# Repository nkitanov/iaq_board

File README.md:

# IAQ (Indoor Air Quality) Board 
IAQ Board is a DIY (Do-It-Yourself) device for measuring internal air quality. I needed a device for measuring some air quality parameters which is **compact, cheap, simple and capable**. After I prototyped it, decided instead of mounting into some odd box with cables hanging inside between the sensors, why not just solder everything on a printed circuit board. I had some experience with this from the time when I was a student years ago and luckily now it's much easier to crate PCB and very cheap to get it printed. 

**And here is my device. I am publishing all the details and documentation under '[open source hardware](https://en.wikipedia.org/wiki/Open-source_hardware)' CC-BY-CA license, so everyone can build, adapt and sell it, as long as share under the same license**
s
**Table of Contents**
   * [IAQ (Indoor Air Quality) Board](#iaq-indoor-air-quality-board)
      * [What exactly is this thing?](#what-exactly-is-this-thing)
      * [Who can build it?](#who-can-build-it)
      * [What about ordering a device?](#what-about-ordering-a-device)
   * [Components Details](#components-details)
      * [1. PCB](#1-pcb)
      * [2. Holder case](#2-holder-case)
      * [3. Microcontroller Board](#3-microcontroller-board)
      * [4. Dust Sensor](#4-dust-sensor)
      * [5. CO2 sensor](#5-co2-sensor)
      * [6. Temperature/Humidity/Pressure sensor](#6-temperaturehumiditypressure-sensor)
      * [7. Ambient Light Sensor](#7-ambient-light-sensor)
      * [8. LEDs](#8-leds)
      * [9. Displays](#9-displays)
      * [10. Volatile Organic Compound sensor](#10-volatile-organic-compound-sensor)
      * [11. Other electrical components](#11-other-electrical-components)
      * [Can you skip components?](#can-you-skip-components)
   * [Bill of Materials (BOM)](#bill-of-materials-bom)
   * [Firmware](#firmware)
   * [Schematic](#schematic)
   * [Soldering tips](#soldering-tips)
   * [User manual](#user-manual)
         * [Multi function button](#multi-function-button)
         * [LED Brightness control and correction](#led-brightness-control-and-correction)
   * [FAQ](#faq)
            * [<em>Can I power it from a battery?</em>](#can-i-power-it-from-a-battery)
            * [<em>Can it be installed outdoors?</em>](#can-it-be-installed-outdoors)
            * [<em>How to calibrate MH-Z19B CO2 sensor?</em>](#how-to-calibrate-mh-z19b-co2-sensor)
            * [<em>How to calibrate SGP30 VOC sensor?</em>](#how-to-calibrate-sgp30-voc-sensor)
            * [<em>How to connect to WiFi?</em>](#how-to-connect-to-wifi)
            * [<em>How to add it in Home Assistant?</em>](#how-to-add-it-in-home-assistant)
            * [<em>What if some of the sensors/displays is disconnected while the device works?</em>](#what-if-some-of-the-sensorsdisplays-is-disconnected-while-the-device-works)
         * [<em>What about short circuits of the exposed electronics?</em>](#what-about-short-circuits-of-the-exposed-electronics)
   * [More Tech Details](#more-tech-details)
   * [Known issues](#known-issues)
   * [License](#license)

## What exactly is this thing?
The device is based on widely available and cheap essential components ([MCU](https://en.wikipedia.org/wiki/Microcontroller) and sensors). The core component is a simple [PCB](https://en.wikipedia.org/wiki/Printed_circuit_board) (printed circuit board) that's why I called it **IAQ Board**. The board integrates all the components in a very small footprint (size of a cigarette box). All parts are soldered on it and everyone can assemble it with basic soldering skills. The total price if you build it yourself is about 50-60 EUR. I also made simplistic holder for 3D print (6-7 EUR is you don't have a 3D printer). For these amount of money you get the following air parameters measured adequately (you might not install all sensors if you want to save money): 
- [X] ***Temperature / Humidity / Pressure***
- [X] [***Air particles PM1, PM2.5, PM10***](https://en.wikipedia.org/wiki/Particulates)
- [X] [***Carbon Dioxide with NDIR sensor***](https://en.wikipedia.org/wiki/Indoor_air_quality#Carbon_dioxide)
- [X] [***Air Quality Index by EPA, based on 24h average PM2.5 particles***](https://airindex.eea.europa.eu/Map/AQI/Viewer/)
- [X] [***Ambient light***](https://en.wikipedia.org/wiki/Illuminance)
- [X] [***Total VOC (volatile organic compound)***](https://en.wikipedia.org/wiki/Volatile_organic_compound)
- [X] ***equivalent CO2 (not very correct compared with the NDIR sensor, but it's provided by the VOC sensor)***

**On top of that:**
- [X] ***At least one OLED display to show the data (can have one more on the top of the MCU board)***
- [X] ***three RGB wide angle LEDs with auto brightness. LED1 indicates PM2.5, LED2 - Air quality index, LED3 - CO2.*** 
- [X] ***auto night dimming of the displays and LEDs (can be disabled)***
- [X] ***MIN/MAX values of Temperature, PM2.5 and CO2, and 24h average PM2.5 value.***
- [X] ***multi function button for selection of the data to show on the display***
- [X] ***[firmware](https://en.wikipedia.org/wiki/Firmware) based on [ESPhome](https://esphome.io/), the device can be [directly added](https://esphome.io/components/api.html) in [Home Assistant](https://www.home-assistant.io/)***
- [X] ***WiFi access to the device with http server and [REST API](https://esphome.io/web-api/index.html) and [esphome native API](https://esphome.io/components/api.html)  to read the sensor data***

Here is a video with all you need to know:

## Who can build it?
The device is just a simple PCB board and almost everyone with some soldering skills can assemble it in a few steps:
1. [Download the PCB files](kicad/) and print the PCB somewhere like https://jlcpcb.com/
2. Buy some components (listed in the bill of materials section) from Aliexpress or any other source.
3. Solder everything on the board. With the exception of the ambient light sensor, all the rest is pretty easy with general soldering skills. Soldering light sensor can be done with regular soldering iron, but because of the small size of the IC, it's easier if you have heat gun or SMD reflow oven/plate. [Here is video how to complete device from assembled PCB.](https://www.youtube.com/watch?v=b2oDBgN3h1w)
4. Flash the microcontroller with the esphome firmware [following the manual](firmware/). You can write your own firmware if you have the skills. :smile: 
5. Print the holder case on 3D printer if you wish. I have some sensors without it and they are perfectly fine, so it's up to you.

If you have experience with electronics and microcontrollers just check the [schematics](kicad/) and make whatever you wish - build your own firmware, do another PCB, connect external sensors, don't use it at all because you can make it better :smile:. The device is quite simple for embedded electronics enthusiasts anyway...

## What about ordering a device?
I made this device for me and then decided to share it. I think a lot of people might be interested to have such air quality sensor. I did not have intension to make money from it, that's why it's "open hardware" and I publish all of the information, so everyone can build it. 

However I know that someone might be interested in the device, but lack the skills to build it. [Please follow this link for more details.](ordering.md)

# Components Details
The device with AAA battery size comparison:

## 1. PCB

The PCB (printed circuit board) is very simple and compact. It's 70x43mm (photos above are showing it larger than the actual size). It just connects a few sensors, microcontroller and displays. I wanted to integrate it in as much smaller footprint as possible, so the whole device is like a cigarette box. Most of the parts are surface mounted which makes the soldering just a bit more complicated, but still not a big deal. And of course it could be integrated even more by soldering all individual components on the PCB but then it's not really a hobby project anymore and much more difficult to build it.
It's designed on [KiCad](https://kicad.org/) and in the [kicad folder](kicad/) you can find full KiCad project, PCB gerber files, etc.
## 2. Holder case

For any device the box is important. However my idea was to expose the PCB and electronics as much as possible in order to simplify it. I like the "raw" view of electronics and in this form I find it beautiful. 

Taking into account this, I designed a simple holder case for "sliding" the PCB in it and holding the particle sensor. The case can stay at about 45 degrees angle. It is designed on Fusion 360 and the [details are here](case_model). The holder case is not perfect, I was thinking to redesign it but no time for this. I am sure someone can do it better. :smile: Or design a complete box to cover the electronics fully, for me it is better in this minimalistic style. 
## 3. Microcontroller Board

Initially I developed the board with using the most popular WiFi enabled MCU [ESP8266](https://en.wikipedia.org/wiki/ESP8266) mounted on the cheap and small [Wemos D1 Mini board](https://docs.wemos.cc/en/latest/d1/d1_mini.html). However this MCU have some limitations described in the [tech details](#more-tech-details), so I changed it with the same size board compatible with Wemos D1 Mini, but running the newer much more powerful MCU of the same company - [ESP32](https://en.wikipedia.org/wiki/ESP32). In that way the device is quite stable, can run web server and since the board is having the same layout, on top of the D1 Mini ESP32 board you can connect extra display designed for d1 mini very easy. PCB is compatible with both D1 Mini ESP8266 or ESP32, even the labels are the same like on the older D1 board. However **I do not recommend to use D1 mini with ESP8266!** Also if I have to build next version of the PCB (I still have some 25 pcs), I will change the pins of one of the dust sensors.

These small size MCU board are pretty nice, they are tiny, have USB connector, onboard power supply and USB converter for programming or serial output. And you are powering the whole device just with a mini USB cable.
## 4. Dust Sensor

Dust sensor is the Chinese [Plantower PMS7003]([http://www.plantower.com/en/content/?110.html](https://www.plantower.com/en/products_33/76.html)) - 1, 2.5 and 10 micron particle laser sensor. It's very small and is perfect for indoor environment. 
## 5. CO2 sensor

Carbon dioxide sensor is the Chinese [Winsen MH-Z19B](https://www.winsen-sensor.com/sensors/co2-sensor/mh-z19b.html) - the most expensive part of the device. It's quite popular for hobby air quality meters and can [adequatly measure](https://www.circuits.dk/testing-mh-z19-ndir-co2-sensor-module/) up to 5000 ppm CO2 concentration.

**Keep in mind that there are some fake MH-Z19B sensors, [explained here](https://revspace.nl/MH-Z19B#Fake_MH-Z19B_.28black_PCB.29).**
## 6. Temperature/Humidity/Pressure sensor

This sensor is the popular [Bosch BME280](https://www.bosch-sensortec.com/products/environmental-sensors/humidity-sensors-bme280/), mounted on 3.3V only breakout board from China. There are also smaller [breakout boards](http://www.cncroutersource.com/breakout-boards.html) from China working both on 5V and 3.3V, but these have voltage regulator which can theoretically warm the board and change the temperature reading. That's why I use the boards with 3.3V only.

**Please note that due to semiconductor shortage these are difficult to find now (June 2021). I am currently using my own breakout where I solder the BME directly. BME280 as IC can be found occasionally in stock from DigiKey**
## 7. Ambient Light Sensor

The light sensor is [TSL 2561](https://ams.com/tsl2561) and it's the only sensor you need to solder directly on the board without a breakout board. I added this sensor not because I need to measure the ambient light but because I am a brightness freak, and I need the LEDs brightness to depend on the ambient light. Also wanted during the night when the lights are off the device to turn off the LEDs and displays automatically. You can also change the behavior of this brightness control and I spend some extra time developing the config only for the brightness features. :smile:
## 8. LEDs

The device have three [Neopixel 5050](https://www.digikey.com/catalog/en/partgroup/neopixel-rgb-5050-led-with-integrated-driver-chip-100-pack/70939) RGB multicolor LEDs. These LEDs are mostly found in the colorful LED strips and are controlled over a single wire. In my esphome based firmware left LED color is indicating the level of PM2.5 and change the colors depending on the value. Middle (LED2) indicates Air Quality Index based on PM2.5 only and the right one (LED3) indicates CO2 value. Keep in mind PM2.5 values are close to [EEA](https://www.eea.europa.eu/) levels (especially AQI). Some other devices like Xiaomi Air Purifiers have some very high levels on their displays and logic - it's green up to 70 microns which is already considered unhealthy both by EEA and EPA. In China "healthy" is considered bellow 50 microns. That's why AUTO mode of these Chinese devices [works so bad](https://smartairfilters.com/en/blog/xiaomi-auto-mode-leaves-air-unsafe-86-hours/). I try to keep indoor PM2.5 around 5-10 microns. I normally control my purifiers by Home Assistant and do not rely on their auto logic. If you have Xiaomi Purifier it can still show green, and the iaq device shows stable red, but it is correct according to the EU regulations.

**Colors of the LEDs depends on this table:**
PM2.5 value (um/m3)<br>LED 1 | [AQI by EEA (Air Quality Index for PM2.5 24h average)](https://airindex.eea.europa.eu/Map/AQI/Viewer/)<br>LED 2 | CO2 value (ppm)<br>LED 3 | Color |  R  |  G  |  B
:-----------------: | :-------------: | :-------------: | :---: | :-: | :-: | :-: 
< 10 | < 10 (Good) | < 700 |  | off | on | off 
11 - 20 | 10 - 20 (Fair) | 700 - 1000 |  | off | on | on 
20 - 30 | 20 - 25 (Moderate) | 1000 - 1500 |  | on | on | off 
30 - 40 | 25 - 50 (Poor) | 1500 - 2100 |  | on | off | on 
\> 50 | > 50 (Very Poor) | > 2100 |  | on | off | off 

## 9. Displays
The main display is the popular SSD1306 128x64 OLED display. On the top of the MCU board you can install extra [OLED 63x48](https://docs.wemos.cc/en/latest/d1_mini_shiled/oled_0_66.html) shield from Lolin which shows temperature, humidity and air pressure only.
## 10. Volatile Organic Compound sensor

This is the [Sensirion SGP30](https://www.sensirion.com/en/environmental-sensors/gas-sensors/sgp30/) senor mounted on a breakout board from China. I do not use it on all my devices, but I added it because I can. :smile: Also with it the device measures almost completely the internal air quality. SGP30 is also showing equivalent CO2 based on VOC but it's not precise compared with MH-Z19B NDIR sensor. Also it needs periodic calibration hardcoded in the firmware which makes it more tricky to use.

Please [check here](https://github.com/nkitanov/iaq_board/issues/10#issuecomment-798994427) for the known issues with these boards.
## 11. Other electrical components

The device have 2 buttons - one for selection screens and settings, and another micro button for calibration of the CO2 sensor to 400ppm if you keep it pressed for more than 7 sec. 

There are also four [surface mounted](https://en.wikipedia.org/wiki/Surface-mount_technology) [bypass capacitors](https://en.wikipedia.org/wiki/Decoupling_capacitor) for the ambient light sensor and the LEDs.

## Can you skip components?
Yes. The minimum you need is the [microcontroller board](#3.-microcontroller-board). However since you don't have any sensors, you won't get any data. :smile: You can add only the sensors needed. Also if you skip ambient light sensor there will be no auto brightness control and the LEDs will operate always at 25% intensity. Installing only the ambient light sensor without any of the displays or any of the other [I2C](https://en.wikipedia.org/wiki/I%C2%B2C) sensors (BME280, SGP30) will not work as there are no [pullup resistors](https://en.wikipedia.org/wiki/Pull-up_resistor) on the PCB for the I2C bus since it uses the resistors of the external breakout boards.

# Bill of Materials (BOM)
Bellow is the list of all parts needed to assemble the device with links to sources where you can get them. Of course other sources can be used, just pay attention that the items are identical with the listed bellow. For example the SSD1306 display can be found with similar physical look and dimensions, but pins are not the same.

Schematic Ref | ITEM | pcs | Comment
--------------| ---- | :-: | -------
| | PCB Board | 1 | in [kicad folder](kicad) you can find all the data and GERBER PCB design files
U1 | [WeMos_D1_mini_ESP32](https://www.aliexpress.com/item/4000880936043.html?spm=a2g0o.productlist.0.0.f387754egZVnTc&algo_pvid=b105e43b-6669-40bc-99c4-cf22d026995d&algo_expid=b105e43b-6669-40bc-99c4-cf22d026995d-6&btsid=0bb0623616009843570355505e4ca0&ws_ab_test=searchweb0_0,searchweb201602_,searchweb201603_) | 1 | [ESP8266 version](https://www.wemos.cc/en/latest/d1/d1_mini.html) also can work but not recommended 
U2 | [PMS7003 Sensor](https://www.aliexpress.com/item/32832444694.html?spm=a2g0s.9042311.0.0.27424c4dKxsO6Z) | 1 | don't use the 2x5pin 1.27mm receptacle which comes normally wit these sensors, explanation is bellow
U3 | [SSD1306 Display](https://www.aliexpress.com/item/32956051129.html?spm=a2g0o.productlist.0.0.523365fcQkP3XC&algo_pvid=b62bd3ab-fe19-479e-bc50-b2c68dd35525&algo_expid=b62bd3ab-fe19-479e-bc50-b2c68dd35525-25&btsid=67d67e08-4ad1-4c08-8cec-e378bae47fc6&ws_ab_test=searchweb0_0,searchweb201602_9,searchweb201603_55) | 1 | pay attention to correct pin order if you are buying from another source, as there are similar 4pin boards with different pinout
U4 | [BME280 breakout board](https://www.aliexpress.com/item/4000166540445.html?spm=a2g0o.productlist.0.0.363a562ely2LZq&algo_pvid=b0bd6068-edbb-4f9c-aa24-92324f726eda&algo_expid=b0bd6068-edbb-4f9c-aa24-92324f726eda-8&btsid=3927b67d-2f89-4594-9f47-b017e00ef8a0&ws_ab_test=searchweb0_0,searchweb201602_9,searchweb201603_55) | 1 | only 3.3V version with 6 pins which have both I2C and SPI. **Please note that due to semiconductor shortage these are difficult to find now (June 2021). I am currently using my own breakout where I solder the BME directly. BME280 as IC can be found occasionally in stock from DigiKey**
U5 | [MH-Z19B Sensor](https://www.aliexpress.com/item/1005001865093513.html?spm=2114.12010610.8148356.5.5b7387a5ZmuUlX) | 1 | **Beware for fake sensors, as [explained here](https://revspace.nl/MH-Z19B#Fake_MH-Z19B_.28black_PCB.29). Buy from Winsen official store in Aliexpress.**  
U6 | [SGP30 breakout board](https://www.aliexpress.com/item/4000004614708.html?spm=a2g0o.productlist.0.0.688164abtt6ZRA&algo_pvid=7f813f70-3c1d-42ee-b6cf-9bf501c47314&algo_expid=7f813f70-3c1d-42ee-b6cf-9bf501c47314-1&btsid=3f683b7d-631a-4373-b0a1-f574cd317549&ws_ab_test=searchweb0_0,searchweb201602_9,searchweb201603_55) | 1
U7 | [TLS2561 light sensor](https://www.aliexpress.com/item/33056165996.html?spm=a2g0s.9042311.0.0.15314c4draqb6x) | 1
C1-C4 | [0.1 uF SMD Capacitor](https://bg.farnell.com/wurth-elektronik/885012207016/cap-0-1-f-10v-10-x7r-0805/dp/2534051?st=smd%20capacitors) | 4
D1-D3 | [Neopixel 5050 LED](https://www.aliexpress.com/item/4000750610574.html?spm=a2g0o.productlist.0.0.55a96722mpqDCp&algo_pvid=4be2d94a-875a-4e56-af12-1f6a3dcdf49f&algo_expid=4be2d94a-875a-4e56-af12-1f6a3dcdf49f-5&btsid=0bb0623416009856118282154ebe61&ws_ab_test=searchweb0_0,searchweb201602_,searchweb201603_) | 3
| SW1 | [Tactile Switch B3S-1000](https://uk.farnell.com/omron/b3s-1000/switch-spno-0-05a-24v-smd/dp/177807) | 1 |
| SW2 | [Tactile Switch B3U-1000P](https://bg.farnell.com/omron/b3u-1000p/switch-spst-no-0-05a-12v-smd/dp/1333652?st=B3U-1000P) | 1
| | [PCB Receptacle, 1.27 mm, 10 Contacts](https://bg.farnell.com/amphenol-icc-fci/20021311-00010t4lf/receptacle-vert-1-27mm-tht-10way/dp/1865313) | 1 | This PCB Receptacle is for connecting PMS7003 dust sensor. Keep in mind these sensors come with such connector included but it's slightly taller and makes a gap of about half mm between sensor and PCB which is not ok.
| | [SMD PCB Receptacle 8 pins](https://uk.farnell.com/samtec/ssm-108-l-sv/receptacle-2-54mm-vert-8way/dp/1668259?st=ssm-108-l-sv%20pcb%20receptacle) | 3 | two are needed for the MCU board, 3rd you can skip. It's for extra pins on the PCB but with ESP32 MCU not needed so much as extra headers can be soldered directly on it's board
| | [PCB Receptacle 4 pin](https://uk.farnell.com/samtec/bcs-104-l-s-te/receptacle-2-54mm-vert-4way/dp/1667470?ost=bcs-104-l-s-te) | 4 | four is needed if all sensors are installed
| | [OLED 63x48 shield](https://www.aliexpress.com/item/32981156326.html?spm=a2g0s.9042311.0.0.27424c4dO21RuC) | 1 | not required, only if you want an extra display on top of the MCU board
| | [Holder case](case_model) | 1 | it's not required to have it but it makes the device completed
| | [Display holder](case_model) | 1 | This small 3D printed part is holding tight the display from flapping 
| | [Various 2.54 headers](https://www.ebay.co.uk/itm/10pcs-40-pin-2-54mm-Breakaway-Male-Header-for-PCB-Breadboard-1x40-Single-Row-UK/262755464818?epid=20008873513&hash=item3d2d723672:g:st8AAOSwMsZdNw5x) | | You will need these for the CO2 sensor if you don't have available. Normally they come together with the breakout boards.
| | [2mm nylon bolts/nuts](https://www.ebay.co.uk/sch/i.html?_from=R40&_trksid=p2047675.m570.l1313&_nkw=2mm+nylon+bolts&_sacat=0) | | If you want to make the display more stable you can install nylon bolts like explained [in the video](https://youtu.be/b2oDBgN3h1w?t=758). Better use [display holder](case_model).

# Firmware
Firmware is created with [ESPHome](https://esphome.io/index.html). The binary file, configuration and instructions are located in [firmware folder](firmware/).

# Schematic
Find all KiCad project in [kicad folder](kicad/) with schematic, PCB design file, 3D models, etc. In schematic U1 (microcontroller board) is based on ESP8266 version (original Wemos D1 mini).

# Soldering tips
You need basic soldering skills and a soldering iron with thin tip. Because most of the components are SMD, it's much easier to buy some [solder paste](https://en.wikipedia.org/wiki/Solder_paste) if you don't have. Most of the SMD components are quite large to solder easily with the iron, you [can look in youtube](https://www.google.com/search?q=solder+smd+components&source=lnms&tbm=vid&sa=X&ved=2ahUKEwien7K4zfbsAhX6BWMBHQMtDZAQ_AUoAnoECBMQBA&cshid=1604964375672299&biw=1600&bih=1097), there are thousand of videos how to solder SMD components. Of course for some parts it's easier to use hotair rework station but not a requirement.

The only more difficult component to solder is the ambient light sensor which is quite small. I normally do these with a thin layer of solder paste and heatgun from bellow. However because of the footpint on the PCB is purposely made a bit bigger, I managed to solder it as well with a regular iron with a thin tip and solder paste. Also magnifying glasses will help.

If you use the small display over the MCU board, make sure i2c address is configured as 0x3D, which means to solder bottom two pads of the solder jumper like here:

# User manual
It's quite simple, the device have only one "multi functional" button SW1, and one micro button SW2 for calibration of the CO2 sensor.

### Multi function button
- Short press "rotates" the data displayed on the right bigger display. By default it starts showing only PM2.5 and CO2 with larger fonts as these are the most important air quality parameters. This is also the default "screen" and every time the device is restarted it will show that screen. The display is quite small (128x64 pixels) so some of the text is shortened like P1 (for PM1), C (for CO2), etc. Each short press of the button rotates this sequence:
```
DEFAULT==================================================================MIN/MAX===============
PM2.5      AQI        Temperature    PM1         Amb.Light  PM1         Temp. MIN        Displays OFF
CO2 ----> Index ----> Humidity ----> PM2.5 ----> TVOC ----> PM2.5 ----> PM2.5 MIN ----> (both displays  
 ^      PM2.5 24h     Pressure       PM10        eCO2       PM10        CO2 MIN          turned off)
 |                                                          Temperature Temp. MAX             |
 |                                                          Humidity    PM2.5 MAX             |
 |                                                          Pressure    CO2 MAX               |
 | _ _ _ _ _ _ _ _ _ _ _ _ _ _ _ _ _ _ _ _ short click_  _ _ _ _ _ _ _ _ _ _ _ _ _ _ _ _ _ _ _|
```

- Press and hold the button from **2 to 5 sec**: On the display you see `LEDs status: OFF`. This means the status LEDs will be tuned off. Do the same to toggle back to `LEDs status: ON`. This setting is saved in the non volatile memory, so it will keep it's setting even if the MCU is restarted. 
- Press and hold the button from **5 to 10 sec**: On the display you see `Night dim: OFF`. This means the LEDs and displays will not be turned off if ambient light fall under 2 lux. Do the same to toggle back to `Night dim: ON`. This setting is saved in the non volatile memory, so it will keep it's setting even if the MCU is restarted. 
- Press and hold from **10 to 15 sec**: On the display you see `MIN-MAX Reset!`. It reset the minimum and maximum values of temperature, PM2.5 and CO2 on screen 6. Please note these resets each time the device is restarted. Keep in mind that 1.5 min after boot and reset, values of CO2 and temperature might not be correct.
- Press and hold from **15 to 20 sec**: It will increase LED brightness correction with +5%. When it reaches +40% another press and hold will make it 0% again. 
- Press and hold from **20 to 30 sec**: On the display for 20 sec it will show the following diagnostic data:
```
YAML ver: (shows version of the esphome yaml config)
ESPHome ver: (ESPHome version which build the firmware)
IP: (IP address if connected to WiFi)
Connected to: (SSID of the wifi, if connected)
LED brightness: (brigtness correction of the LEDs)
```
### LED Brightness control and correction
Led brightness is controlled periodically (each 3 sec), proportional of the ambient light measured by the TLS2561 sensor. If there is no ambient light sensor installed LEDs are constant at 25%, but auto turn off will also not work. Logic of this simple auto control is configured in [this code](firmware/includes/brightness.yaml).

Also by default setting of these LEDs are to begin from 11% brightness. If it's bellow 11% they are turned off. As mentioned in the LED description setting these Chinese LEDs comes with different intensity and the ones listed in Bill of Materials section are too weak at the lowest setting. That's why I added brightness correction setting which can go from 0% to +40% in 5% step. This be done with press and hold the multi function button from 15 to 20 sec (explained above). This setting is saved in the non volatile memory of the MCU and it does not have to be configured after each reset. Alternatively if the device is added in Home Assistant, you will see a template switch called `brightness_correction`, which is doing exactly the same thing as the button on pin.

# FAQ
#### *Can I power it from a battery?*

The device is powered from regular micro USB cable with 5V and consumes between 100-250 mA. You can power it with USB battery pack but not for too long (for example 4000 mAh battery will be depleted in about 20h). If you need to operate it from a battery, firmware have to enter the MCU in a [deep sleep](https://esphome.io/components/deep_sleep.html) mode periodically. You have to build your own firmware. I do not run any of my devices in deep sleep as I do not see a reason for that.
#### *Can it be installed outdoors?*

The device is not waterproof. It can run outdoors if you install it in enclosure which is protecting it from water. It can handle high humidity maybe (never tested it). However the main purpose of the device is to be an internal air quality monitor. Measuring CO2 and VOC outside does not makes too much sense, but it can be used for dust pollution monitoring.

#### *How to calibrate MH-Z19B CO2 sensor?*

Periodically (let's say one time per month) and after installation of a new sensor calibration needs to be performed. The calibration is done by exposing it to the outside air which have about 400ppm CO2 concentration for about 20-30 min and then press and hold the micro button SW2 for more then 7 sec. In that way the value of the sensor is "zeroed" at 400 ppm. Alternatively if the device is added in Home Assistant, there is a template switch called `switch.co2_sensor_zero_calibration` and you just turn it on. It's doing the same as pusing the button but you are doing it remotely over the WiFi. [Here](https://www.circuits.dk/testing-mh-z19-ndir-co2-sensor-module/) are more details about this sensor and calibration.

#### *How to calibrate SGP30 VOC sensor?*

It's explained in [ESPHome manual](https://esphome.io/components/sensor/sgp30.html). You need periodically to update the firmware which is quite easy if you use Home Assistant. In my initial tests I noticed even without calibration value, the sensor shows some values and can detect smells, alcohol vapors, etc. 

#### *How to connect to WiFi?*

After 1 minute of unsuccessful WiFi connection attempts, the microcontroller will start a WiFi hotspot with name `iaq_device` and password `12345678`. When you connect to this fallback hotspot, the web interface should open automatically (see also login to network notifications). If that does not work, you can also navigate to http://192.168.4.1/ manually in your browser. Then type name and password of your local wifi hotspot, click save and MCU will restart and try to connect to the provided network. Additionally from this captive portal you can upload a new firmware.

#### *How to add it in Home Assistant?*

If you have Home Assistant you have to [install the ESPHome addon](https://esphome.io/guides/getting_started_hassio.html), and after that [add the device](https://esphome.io/components/api.html). All sensors, switches, LEDs will appear automatically as entities in Home Assistant. Then you can add them on the dashboard, here is one of my devices added on Home Assistant dashboard with all data from it.

#### *What if some of the sensors/displays is disconnected while the device works?*

Some of the sensors can be accidentally disconnected as on the original design they are not soldered on the PCB but are connected on a header receptacle. No worries with that. On the display you will see `NaN` and it means there is no value from the sensor or it's out of boundaries. Just reseat the sensor and push the reset button on the MCU board or  disconnect and reconnect the USB cable.

### *What about short circuits of the exposed electronics?*

Since all the components are exposed, there is some risk of making a short circuit with a metal object. The power supply is just 5V with limited current so it shouldn't be a big worry. However be careful not to short circuit anything with a conductive object as theoretically this can damage a component. 

# More Tech Details

As I mentioned above the initial design was based on ESP8266 microcontroller. Because of that the PCB is developed for [Wemos D1 Mini board](https://docs.wemos.cc/en/latest/d1/d1_mini.html). Later on I decided it's much better to use ESP32 version, but PCB is not yet redeveloped and PCB silkscreen (writings) is for Wemos D1 Mini with esp8266. 
- J1 external pins was added for some extra pins available on Wemos D1 Mini for eventual connection of external sensors, inputs and outputs. These are all free left pins on esp8266 version. ESP32 version of D1 mini have 2 rows of pin which are directly usable and since there is no place on the PCB, only J1 will stay. The designations D8, D3, A0 are matching Wemos D1 mini ESP8266
- Because of the limitations with only one hardware UART port (which is physically available only on 2 specific pins) of the ESP8266, the dust sensor is using the hardware pins, which are shared with the Wemos D1 USB to UART converter. As a result the uart output of the firmware is disabled and it's not possible to flash the device over USB while it's connected on the PCB. It needs to be disconnected from the PCB and then it can be flashed over the USB. On ESP32 there are 3 dedicated hardware UARTs configuarable on any pin so if I do a next version of the PCB, it will be only for ESP32 and I will free up the USB converter ports for debugging. 
- In the description of [WeMos_D1_mini_ESP32](https://www.aliexpress.com/item/4000880936043.html?spm=a2g0o.productlist.0.0.f387754egZVnTc&algo_pvid=b105e43b-6669-40bc-99c4-cf22d026995d&algo_expid=b105e43b-6669-40bc-99c4-cf22d026995d-6&btsid=0bb0623616009843570355505e4ca0&ws_ab_test=searchweb0_0,searchweb201602_,searchweb201603_) the pins for UART0 are crossed (TX is where RX is shown). It's easy to fix as you can select those pins but if you carefully check the pins you might wonder why is that.
- If ESP8266 version is used there is no second dedicated hardware UART (we need two - one for dust sensor, and one for CO2 sensor). As a result the second one is "software" UART port, which uses [bit banging](https://en.wikipedia.org/wiki/Bit_banging). in combination with the WiFi activity it causes periodic WDT resets of the MCU - sometimes a few times for a few hours which is annoying. And this is one of reasons I use ESP32 now and do not recommend ESP8266.
- on the PCB there are no pullup resistors on the I2C bus. All breakout boards have these pullup resistors, so even attaching only one is enough. However if we install only the ambient light sensor and nothing more, it won't work because there will be no pullups. Also if you add more i2c breakout boards keep an eye of the resistance as it will drop with each extra resistor like [described here](https://www.bluedot.space/tutorials/how-many-devices-can-you-connect-on-i2c-bus/).
- ESP8266 is quite unstable if you try to use AP mode, also enabling http server is too much for this processor. That's why - don't use it, use only ESP32. :smile:
- JP1 solder jumper is for changing i2c slave address of the ambient light sensor. In the datasheet of the sensor are described the different configuration. The default address is when JP1 is not soldered.

# Known issues
These are valid for ESP32 MCU:
- Poor quality of the SGP30 VOC sensor breakout boards from China. The issues and fixes [explained here](https://github.com/nkitanov/iaq_board/issues/10#issuecomment-798994427).
- When you open [the web interface](https://esphome.io/components/web_server.html) of the device - it resets sometimes.
- I had a batch of Neopixel 5050 LEDs which are a bit brighter than the one linked in the BOM section and sometimes they switch to white color and 100% intensity. This is fixed in max 3 sec when correct color and brightness is set back again. These LEDs are set sequentially by their protocol so apparently it interprets wrongly set command or something. This is not happening with the LEDs linked in BOM but keep it in mind that it can happen with some LEDs (especially if they are from a bright batch).
- In the configuration I run the temperature with -1 degreeC offset. I found out these sensors shows a bit higher, and also there is some minimal temperature rise from conducted heat from the PCB. Always connect the BME280 sensor high above the PCB as in my design with the 4 pin receptacle. If you solder it lower on the PCB it might run hotter. For even more precise temperature measurement you can calibrate in esphome the value very precisely if you have access to calibrated thermometer. I was thinking also to experiment with thermocouple on the hole of the dust sensor fan so it can not pick up extra heat. This is in case if you need to use this temperature as input for a thermostat, as I do. 

These are valid for ESP8266 MCU (including the previous issues), not recommended to use that MCU because of the bellow issues:
- periodic [WDT resets](https://en.wikipedia.org/wiki/Watchdog_timer) depending of the WiFi activity, if MCU not connected to WiFi, it's ok. This is caused by the bit banging of the UART interface.
- web server is almost unusable as it needs a lot of memory which is not available on this tiny MCU
- unstable [AP fallback mode](https://esphome.io/components/wifi.html#access-point-mode), causing WDT resets, so sometimes not easy to connect to WiFi without hardcoding the credentials in the firmware

# License 
The device is [Open-source hardware](https://en.wikipedia.org/wiki/Open-source_hardware), [licensed by Open Source Hardware Association](https://certification.oshwa.org/bg000078.html). 

- Hardware is licensed under [CERN-OHL-W v2](https://ohwr.org/cern_ohl_w_v2.txt).
- Software is licensed under [Apache License 2](https://www.apache.org/licenses/LICENSE-2.0)
- Documentation is licensed under [CC-BY-SA-4.0](https://creativecommons.org/licenses/by-sa/4.0/).

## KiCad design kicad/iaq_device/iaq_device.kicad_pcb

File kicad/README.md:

# KiCad project design

This folder contains [KiCad](https://www.kicad.org/) project in [iaq_device folder](iaq_device) - schematic, [datasheets](iaq_device/datasheets) and [gerber](iaq_device/plot) files.

In order to print the PCB you have to zip all files from plot folder, these are the gerber files. Then upload the zip like [explained here](https://support.jlcpcb.com/article/21-how-do-i-place-an-order) for JLCPCB.

In the folder [my_libs](my_libs) are the custom footprint and symbol libraries, 3D models for kicad 3D viewer.

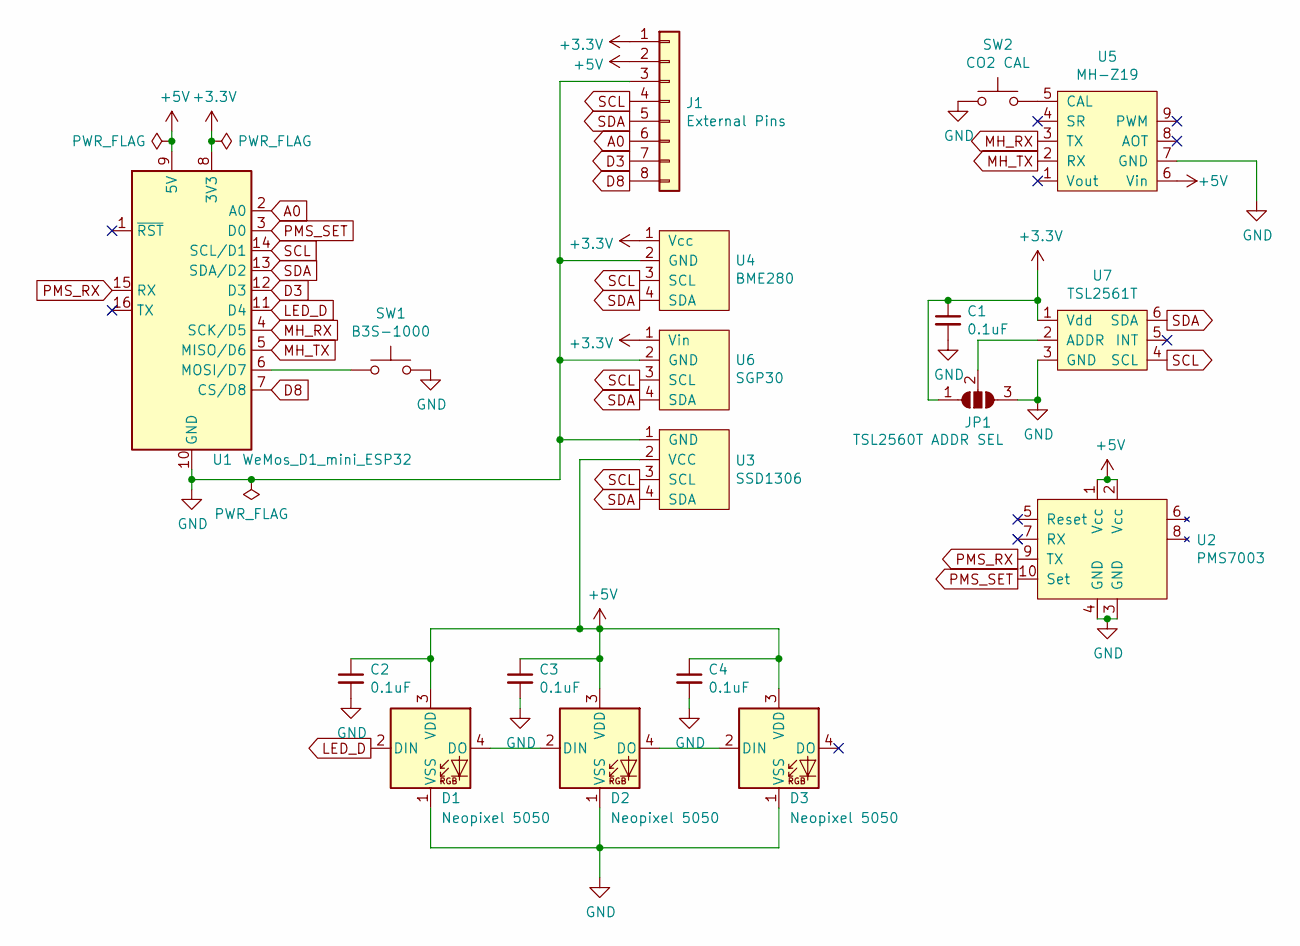
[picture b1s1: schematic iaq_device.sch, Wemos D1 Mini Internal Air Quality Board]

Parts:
C1, C2, C3, C4: 0.1uF; C_0805_2012Metric
D1, D2, D3: Neopixel 5050; LED_Inolux_IN-PI554FCH_PLCC4_5.0x5.0mm_P3.2mm
J1: External Pins; PinSocket_1x08_P2.54mm_Vertical_SMD_Pin1Left
JP1: TSL2560T ADDR SEL; SolderJumper-3_P1.3mm_Open_RoundedPad1.0x1.5mm_NumberLabels
SW1: B3S-1000; SW_SPST_B3S-1000
SW2: CO2 CAL; SW_SPST_B3U-1000P
U1: WeMos_D1_mini_ESP32; WEMOS_D1_surface
U2: PMS7003
U3: SSD1306
U4: BME280; BME280_breakout_6pin
U5: MH-Z19
U6: SGP30; SGP30_breakout_4pin
U7: TSL2561T

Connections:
+3V3: C1.1, J1.1, JP1.1 (A), U1.8 (3V3), U4.1 (Vcc), U6.1 (Vin), U7.1 (Vdd)
+5V: C2.1, C3.1, C4.1, D1.3 (VDD), D2.3 (VDD), D3.3 (VDD), J1.2, U1.9 (5V), U2.1 (Vcc), U2.2 (Vcc), U3.2 (VCC), U5.6 (Vin)
A0: J1.6, U1.2 (A0)
D3: J1.7, U1.12 (D3)
D8: J1.8, U1.7 (CS/D8)
GND: C1.2, C2.2, C3.2, C4.2, D1.1 (VSS), D2.1 (VSS), D3.1 (VSS), J1.3, JP1.3 (B), SW1.2, SW2.1, U1.10 (GND), U2.3 (GND), U2.4 (GND), U3.1 (GND), U4.2 (GND), U5.7 (GND), U6.2 (GND), U7.3 (GND)
LED_D: D1.2 (DIN), U1.11 (D4)
MH_RX: U1.4 (SCK/D5), U5.3 (TX)
MH_TX: U1.5 (MISO/D6), U5.2 (RX)
unnamed: D1.4 (DO), D2.2 (DIN)
unnamed: D2.4 (DO), D3.2 (DIN)
unnamed: JP1.2 (C), U7.2 (ADDR)
unnamed: SW1.1, U1.6 (MOSI/D7)
unnamed: SW2.2, U5.5 (CAL)
PMS_RX: U1.15 (RX), U2.9 (TX)
PMS_SET: U1.3 (D0), U2.10 (Set)
SCL: J1.4, U1.14 (SCL/D1), U3.3 (SCL), U4.3 (SCL), U6.3 (SCL), U7.4 (SCL)
SDA: J1.5, U1.13 (SDA/D2), U3.4 (SDA), U4.4 (SDA), U6.4 (SDA), U7.6 (SDA)

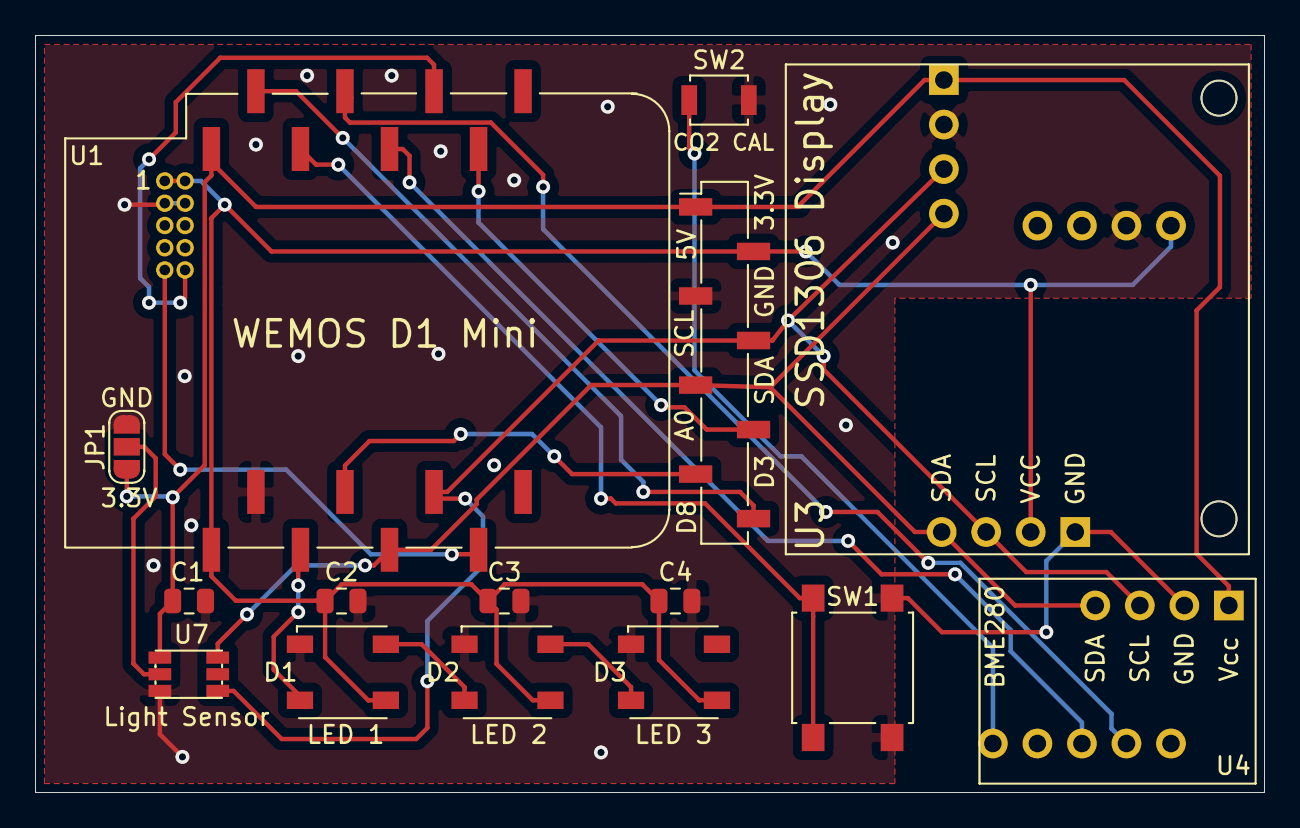
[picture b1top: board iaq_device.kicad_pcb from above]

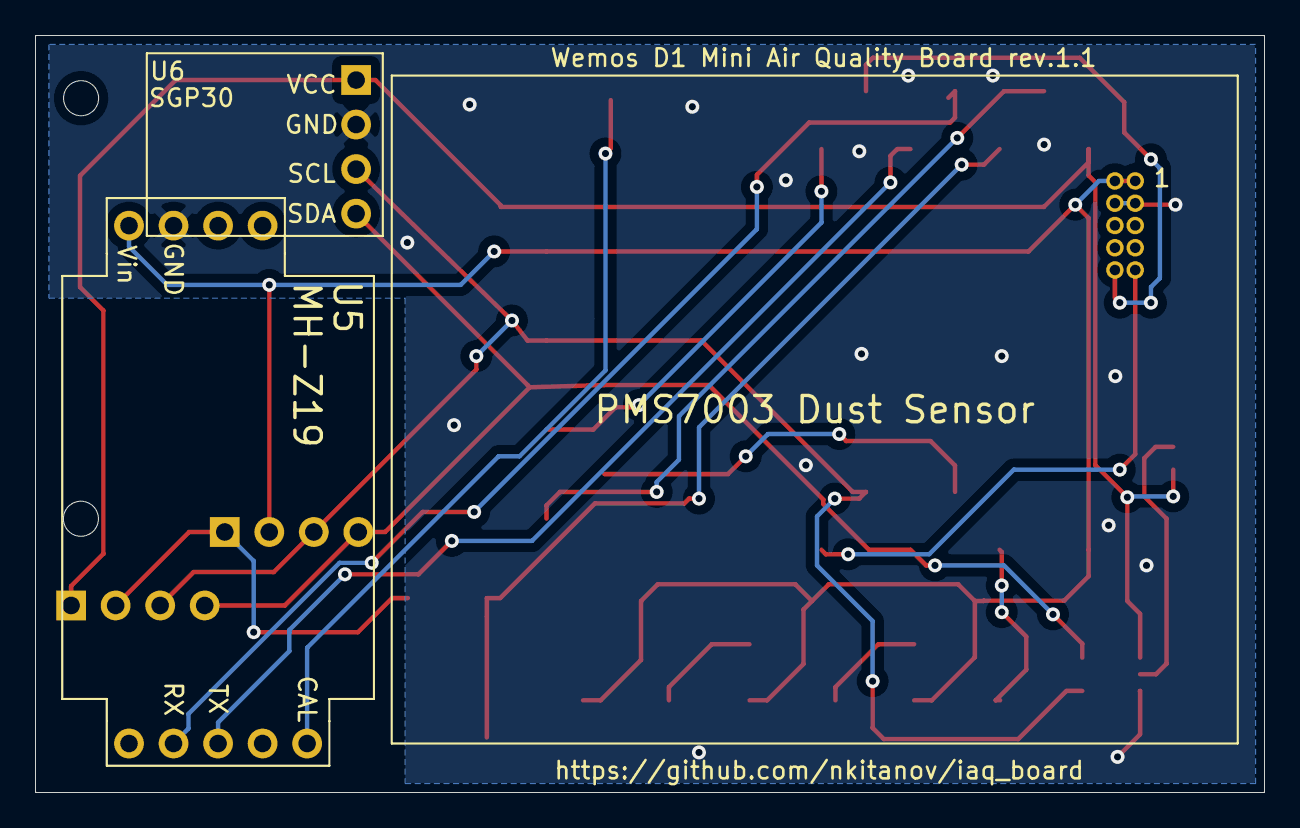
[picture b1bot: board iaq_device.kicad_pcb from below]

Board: 2 copper layers, 70.1 x 43.2 mm, 18 parts (3 on the bottom side), 18 nets.

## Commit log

2020-09-25 add gitignore
2020-09-25 remove cached ignored file
2020-09-29 update kicad readme
2020-09-29 add gerbers folder
2020-10-12 update firmware
2020-11-01 adding toc
2020-11-10 final updates
2020-11-10 update emoji
2020-11-10 add counter
2020-11-23 add ordering option
2020-11-23 add ordering
2020-12-05 update fw with new esphome ver
2020-12-13 update with assemble the PCB video
2020-12-13 add video
2021-02-05 docs: correct led state for worst air condition
2021-02-22 add note for fake MH-Z19B sensor and update the license info
2021-02-22 modify license wording
2021-03-14 * updated SGP30 known issues * updated ordering information
2021-03-24 update fw md
2021-03-24 add display holder 3d model
2021-04-05 update bom, add better photo of complete device
2021-04-21 Update case:
    - make channels for the PCB slacker so it can fit easily
    - increase angle of the pin so the case can stand more stable when angled
    - increase width of the pin to 12 mm
2021-06-04 update BME280 info
2021-06-04 update BME280 shortage info
2021-06-14 fix image
2021-06-17 update license info
2021-06-19 add license info
2021-09-01 update ordering
2021-11-07 update details
2021-11-07 fi typo
2021-11-08 Update README.md
    https://forum.kicad.info/t/warning-avoid-all-links-to-kicad-pcb-org-use-kicad-org/31521
2022-10-03 Update iaq_board.yaml
    Added variant for neopixelbus
2023-01-24 Fix PMS7003 link
2024-01-20 Update iaq_board.yaml
    Add HA Requirements and fix ;
    Firmware doesnt compile on 2022.12.X ESPHome - linking problem #27
2024-01-20 Update iaq_board.yaml
    Modernised Yaml + Reformatted for better editing of env configs (wifi+keys)
2024-01-23 nkitanov's last version
2024-01-23 Rename iaq_board.yaml to iaq_board-1.1.3.yaml
2024-01-23 Rename iaq_board.bin to iaq_board-1.1.3.bin
2024-01-23 Update iaq_board.yaml
    Added Virtual Buttons to simulate physical button hold functions
2024-01-23 Update iaq_board.yaml
    Update GPIO ID; button > buttonpcb
    error is ID 'button' conflicts with the name of an esphome integration, please use another ID name. Due to addition of virtual buttons being used
2024-01-23 Update iaq_board.yaml
    Last PR pulled a bad version - this is tested as working;
    Changes- Changed Button in binary sensor to buttonPCB to fix a complication error with the ESPhome 'button:' id
2024-01-23 Update iaq_board.yaml
    Added missing button to change to the next screen (Part of future idea to rotate the screen on an interval)
2024-01-23 Update iaq_board.yaml
    Updated Icons
2024-01-23 Create HA-Next Screen
    Automation example for automatic screen changing, reduces burn in and adds a feature
2024-01-23 Rename HA-Next Screen to Screen-Automation.yaml
2024-01-23 Update README.md
    added changes I've made
2024-02-21 Update iaq_board.yaml
    breaking change in esphome support of bme280 fixed
2024-03-28 test
2024-11-11 Revert "Update iaq_board.yaml for ESPHome 2024.10.0"
    This reverts commit 5ceda27facfb37ea441ae7d13d907912b07ded71.
    Revert this as it overwrite bugfixes

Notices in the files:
README.md:
License:
The device is [Open-source hardware](https://en.wikipedia.org/wiki/Open-source_hardware), [licensed by Open Source Hardware Association](https://certification.oshwa.org/bg000078.html).
- Hardware is licensed under [CERN-OHL-W v2](https://ohwr.org/cern_ohl_w_v2.txt).
- Software is licensed under [Apache License 2](https://www.apache.org/licenses/LICENSE-2.0)
- Documentation is licensed under [CC-BY-SA-4.0](https://creativecommons.org/licenses/by-sa/4.0/).
